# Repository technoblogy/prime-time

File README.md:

# Prime Time
A digital clock based on two 8x8 bi-colour LED dot matrix displays.

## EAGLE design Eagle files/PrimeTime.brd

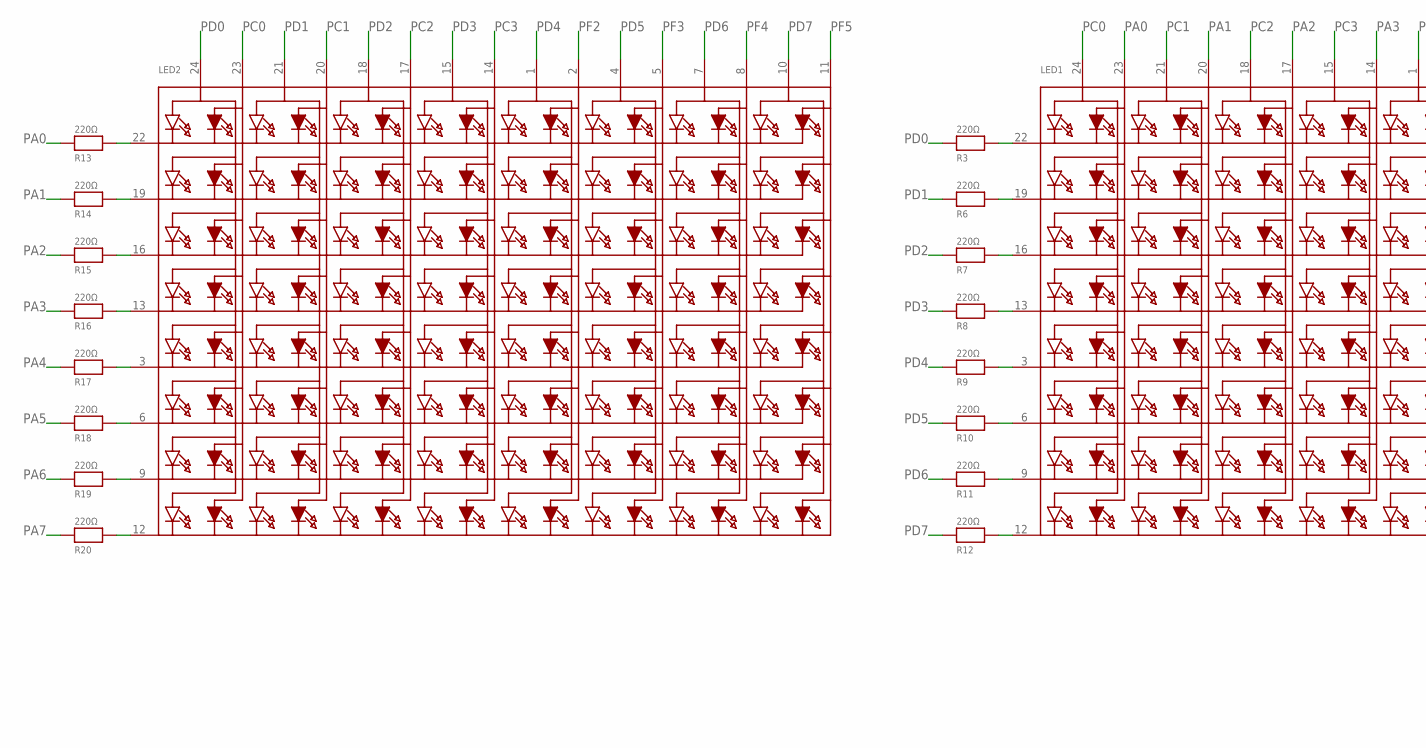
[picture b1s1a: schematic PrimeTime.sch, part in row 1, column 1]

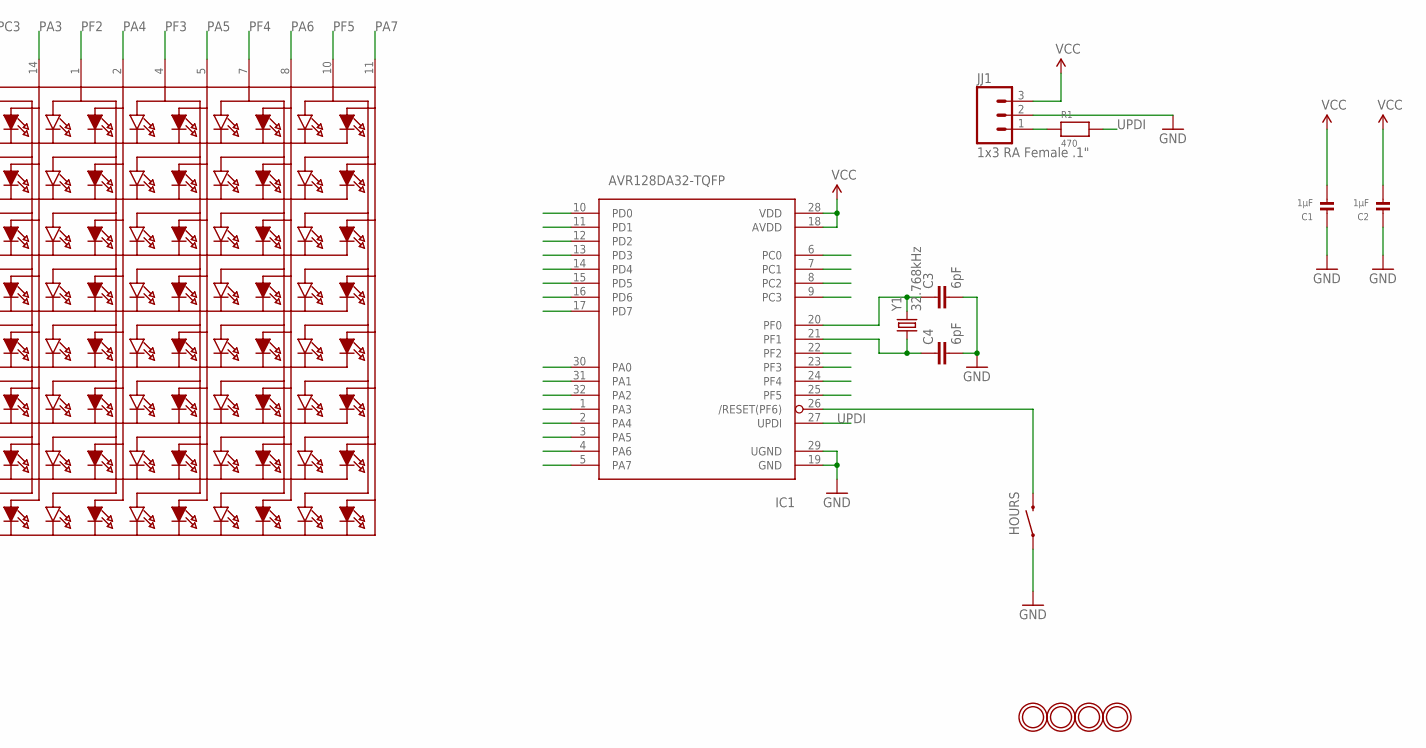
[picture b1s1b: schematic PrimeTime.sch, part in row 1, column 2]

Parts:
C1, C2: 1µF; _0805MP
C3, C4: 6pF; 0805
HOURS: SWITCH-MOMENTARY-2SMD-4; TACTILE_SWITCH_TALL
IC1: AVR128DA32-TQFP; TQFP32-08
JJ1: 1x3 RA Female .1"; 1X03_SMD_RA_FEMALE
LED1, LED2: SEGMENT_8X8_BICOLOR_ROWCATHODEMI2A883XX; SEGMENT_BICOL_BL-M12A883XX
R1: 470; _0805MP
R3, R6, R7, R8, R9, R10, R11, R12, R13, R14, R15, R16, R17, R18, R19, R20: 220Ω; _0805MP
U$1, U$4, U$5, U$9: MOUNTINGHOLE2.5; MOUNTINGHOLE_2.5_PLATED
Y1: 32.768kHz; CRYSTAL-SMD-3.2X1.5MM

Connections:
GND: C1.1, C2.1, C3.2, C4.2, HOURS.A2 (1), IC1.19 (GND), IC1.29 (UGND), JJ1.2
unnamed: LED2.22 (K1), R13.2
unnamed: LED2.19 (K2), R14.2
unnamed: LED2.16 (K3), R15.2
unnamed: LED2.13 (K4), R16.2
unnamed: LED2.3 (K5), R17.2
unnamed: LED2.6 (K6), R18.2
unnamed: LED2.9 (K7), R19.2
unnamed: LED2.12 (K8), R20.2
unnamed: HOURS.B2 (2), IC1.26 (/RESET(PF6))
unnamed: LED1.22 (K1), R3.2
unnamed: LED1.19 (K2), R6.2
unnamed: LED1.16 (K3), R7.2
unnamed: LED1.13 (K4), R8.2
unnamed: LED1.3 (K5), R9.2
unnamed: LED1.6 (K6), R10.2
unnamed: LED1.9 (K7), R11.2
unnamed: LED1.12 (K8), R12.2
unnamed: C4.1, IC1.21 (PF1), Y1.P$1 (1)
unnamed: C3.1, IC1.20 (PF0), Y1.P$2 (2)
unnamed: JJ1.1, R1.1
PA0: IC1.30 (PA0), LED1.23 (A2), R13.1
PA1: IC1.31 (PA1), LED1.20 (A4), R14.1
PA2: IC1.32 (PA2), LED1.17 (A6), R15.1
PA3: IC1.1 (PA3), LED1.14 (A8), R16.1
PA4: IC1.2 (PA4), LED1.2 (A10), R17.1
PA5: IC1.3 (PA5), LED1.5 (A12), R18.1
PA6: IC1.4 (PA6), LED1.8 (A14), R19.1
PA7: IC1.5 (PA7), LED1.11 (A16), R20.1
PC0: IC1.6 (PC0), LED1.24 (A1), LED2.23 (A2)
PC1: IC1.7 (PC1), LED1.21 (A3), LED2.20 (A4)
PC2: IC1.8 (PC2), LED1.18 (A5), LED2.17 (A6)
PC3: IC1.9 (PC3), LED1.15 (A7), LED2.14 (A8)
PD0: IC1.10 (PD0), LED2.24 (A1), R3.1
PD1: IC1.11 (PD1), LED2.21 (A3), R6.1
PD2: IC1.12 (PD2), LED2.18 (A5), R7.1
PD3: IC1.13 (PD3), LED2.15 (A7), R8.1
PD4: IC1.14 (PD4), LED2.1 (A9), R9.1
PD5: IC1.15 (PD5), LED2.4 (A11), R10.1
PD6: IC1.16 (PD6), LED2.7 (A13), R11.1
PD7: IC1.17 (PD7), LED2.10 (A15), R12.1
PF2: IC1.22 (PF2), LED1.1 (A9), LED2.2 (A10)
PF3: IC1.23 (PF3), LED1.4 (A11), LED2.5 (A12)
PF4: IC1.24 (PF4), LED1.7 (A13), LED2.8 (A14)
PF5: IC1.25 (PF5), LED1.10 (A15), LED2.11 (A16)
UPDI: IC1.27 (UPDI), R1.2
VCC: C1.2, C2.2, IC1.18 (AVDD), IC1.28 (VDD), JJ1.3

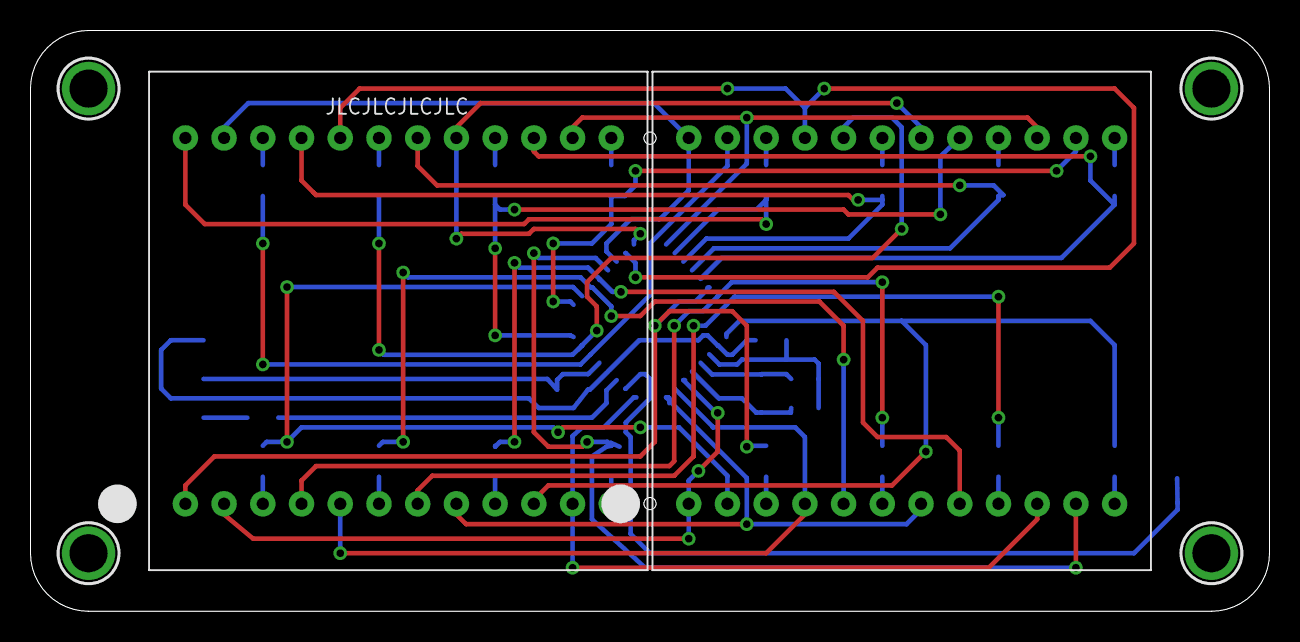
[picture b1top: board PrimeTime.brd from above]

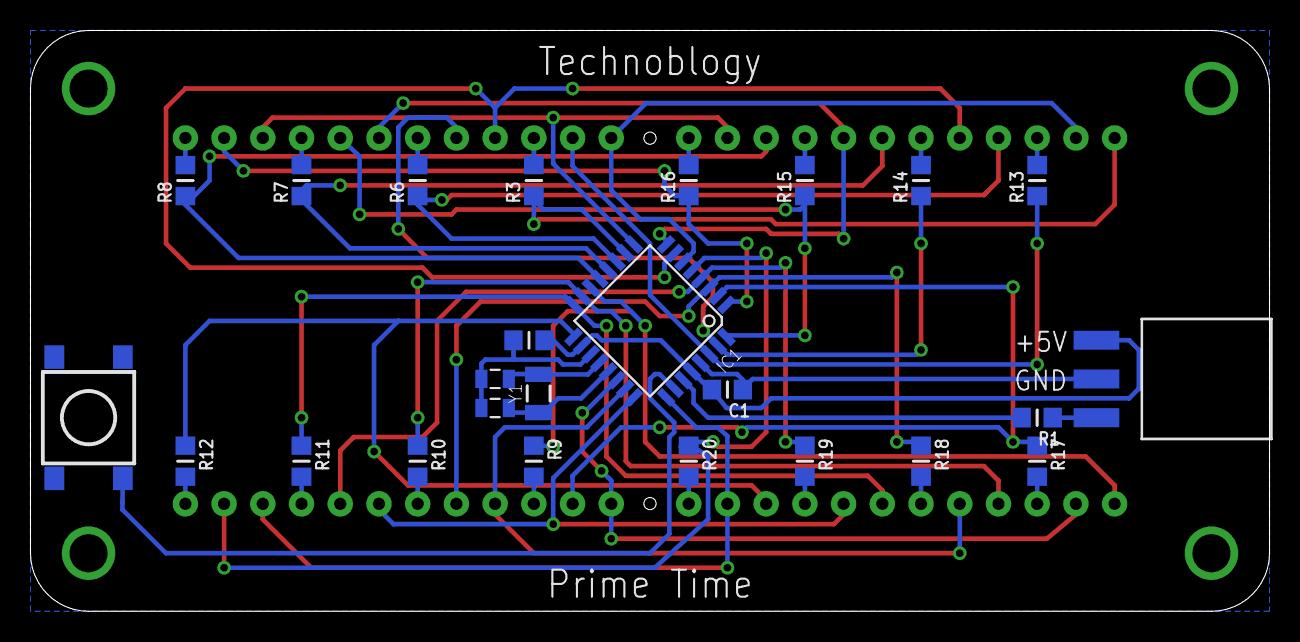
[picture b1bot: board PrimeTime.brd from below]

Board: 2 copper layers, 81.3 x 38.1 mm, 31 parts (25 on the bottom side), 47 nets.

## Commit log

2025-03-04 Version 1

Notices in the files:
parts and their libraries:
SparkFun-Electromechanical: Licensing: Creative Commons ShareAlike 4.0 International - https://creativecommons.org/licenses/by-sa/4.0
microbuilder: This work is placed in the public domain, and may be freely used for commercial and non-commercial work with the following conditions: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
